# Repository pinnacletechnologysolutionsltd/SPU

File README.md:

# SPU

SPU is an experimental computing architecture exploring how exact algebraic
arithmetic, geometric representations and deterministic transformations can
support useful native computational primitives.

The [research identity](docs/RESEARCH_IDENTITY.md) defines **Demonstrated**,
**Experimental** and **Exploratory** claims and the evidence needed for utility
in correctness, determinism, speed, energy, verification or system complexity.

Architectural invention is the ambition; demonstrated utility is the test.

## SPU v0.2: canonical machine, the Gen-1 Surd CPU

Each SPU release identifies one canonical machine, its architectural contract and
the evidence for it. For v0.2 that machine is the **Gen-1 Surd CPU**. It is
deliberately narrow, and it is the reference point for everything this release
claims about the processor.

| Property | SPU v0.2 |
|---|---|
| Machine | Frozen Gen-1 Surd CPU ([architectural contract](docs/GEN1_ARCHITECTURAL_CONTRACT.md); [source package](hardware/boards/artix7/wukong_v3/cpu_v02/README.md)) |
| Arithmetic | Exact multiplication in Q(√3), (a + b√3)/d with 64-bit fields: raw results that fit are committed unreduced, otherwise exact normalization-to-fit, otherwise refusal |
| Programming model | One architectural register (S0); four accepted instruction forms (SLI, SLD, SMUL, SRD); a fixed 14-instruction ROM program built into the bitstream; no control flow |
| Output | One 33-byte UART frame per reset (success or fault) |
| FPGA | Artix-7 XC7A100T on a Wukong V3 board, configured over JTAG into SRAM |
| Simulator | C++ `spu_vm --profile gen1-surd` ([usage](docs/software_guide.md)); conforms to the registered RTL fixtures and recorded silicon frames (software conformance only) |
| Physical status | Experimental single-unit observations: golden program and operand variants, repeated reloads, scoped reset recovery (ledger §3.40–3.43, §3.47–3.49, §3.51–3.52, starting at [§3.40](docs/hardware_evidence.md#340--cpu-board-4c-r1-first-fixed-program-surd-cpu-run-over-uart-2026-10-30)); nominal routed timing analysis; bit-exact rebuild of the configuration payload |
| Not established | General CPU qualification, flash boot, I/O and reset timing, metastability, multiple units |
| Release status | SPU v0.2.0, experimental Gen-1 Surd CPU; see the [v0.2.0 release](https://github.com/pinnacletechnologysolutionsltd/SPU/releases/tag/v0.2.0) and the [readiness record](docs/V02_RELEASE_READINESS.md#12-publication-record-2026-11-11) |

## SPU v0.3: programmable-surd CPU (in preparation)

This branch adds the v0.3 `programmable-surd` machine beside the v0.2 Gen-1 CPU above. v0.3 is a
programmable exact-arithmetic processor with a verified toolchain. It is experimental, it makes no
performance claim, and this branch has not been published as a release.

| Property | SPU v0.3 (`programmable-surd`) |
|---|---|
| Contract | [Frozen v0.3 contract](docs/design/SPU_V03_CONTRACT_CANDIDATE.md): the authoritative ISA. The other `SPU_V03_*` design records in `docs/design/` are historical provenance, not current requirements |
| Machine | Sequential, multicycle, in-order; eight Surd registers S0–S7; programs of 1–256 words; no data memory |
| Arithmetic | Bounded exact Q(√3), (a + b√3)/d with 64-bit fields. A refused `SMUL`, `SADD` or `SSUB` leaves its destination unchanged and sets the refusal flags; the program must check them |
| Inputs | A program image and an instruction budget, supplied by the host. There is no general runtime operand input: input values are part of the image |
| Tools | [SDK](software/sdk/README.md) (assembler, disassembler, `spu` CLI), C++ `spu_vm --profile programmable-surd`, a Python oracle and a UART host client |
| Examples | [`software/sdk/examples/`](software/sdk/examples/): exact √3 arithmetic (Pell K=33), exact orientation, and a refusal-and-recovery branch (Pell K=34) |
| Physical status | One recorded session on one Wukong unit and one SDK-driven run (ledger §3.53 and §3.54 in [`docs/hardware_evidence.md`](docs/hardware_evidence.md)): observations, not a qualification |
| Not established | Qualification of the UART interface, timing margin or reset behaviour; operation across reloads, supply or temperature; multiple units |

The rational GPU, HEX-SOM, the experimental H0 programmable image and the wider
mathematical research below are **experimental components**. They are not
features of the canonical CPU.

Where any historical document in this repository (for example earlier ISA, rotor or accelerator descriptions) conflicts with the Gen-1 architectural contract, the contract is authoritative for v0.2; historical documents are kept for provenance, not as descriptions of supported hardware.

## What is here

- **A software stack.** A Python virtual machine, a C++ VM with the `gen1-surd`
  profile for the canonical machine, an assembler, an exact robotics chain and an
  offline GPU model, all runnable without any hardware.
- **Verilog and FPGA builds** for Tang Primer 25K and Wukong Artix-7 boards. The
  canonical v0.2 machine is the Gen-1 Surd CPU above. The experimental H0
  programmable image is a separate configuration with its own single-session
  observation, not part of the canonical release.
- **Exact-geometry and classification work**, with its limits stated in the
  [capability matrix](docs/CAPABILITY_MATRIX.md), which separates mathematical
  argument, host software, RTL simulation, FPGA synthesis and physical hardware,
  because none implies another.

## Try it in two minutes

You need Python 3.10 or newer and Git. Cloning requires network access; the
commands that follow run locally without a board or package installation.
This README describes the curated `release/v0.3` branch, which carries the v0.2 release
content plus the v0.3 additions listed above; other branches may contain a different snapshot.

```bash
git clone https://github.com/pinnacletechnologysolutionsltd/SPU.git && cd SPU
python3 software/spu_vm_test.py          # ends with "N passed, 0 failed" and PASS
python3 -m software.spu_gpu_eval.cli device-preview examples/gpu/t1d_two_triangle.json \
    --out build/gpu_evaluation/first_run
python3 -m software.spu_gpu_eval.cli inspect examples/gpu/t1d_two_triangle.json --x 320 --y 0
```

The second command renders a two-triangle scene twice: once as an exact mathematical
reference and once through a finite-width model of the GPU's depth arithmetic. Open
`build/gpu_evaluation/first_run/device_preview.ppm` in any image viewer. The last command
shows one pixel where both paths agree on the winner and colour but differ in depth
(2000 versus 1999). The [software quickstart](docs/NEWCOMER_SOFTWARE_QUICKSTART.md) lists more
commands, including a robotics chain and a scene edit, with expected output. Use a new
`--out` directory for each run.

## Known limitations

State these before citing any result:

- **The CPU is not qualified.** The Gen-1 evidence consists of single-unit board
  observations of a fixed program, plus nominal timing analysis. It does not cover
  general correctness, flash boot, I/O or reset timing, or more than one board. The
  separate experimental H0 image ran two UART-loaded programs in one session
  ([§3.46](docs/hardware_evidence.md#346--h0-board-uart-3b-first-uart-loaded-programmable-h0-cpu-run-on-wukong-2026-11-03-utc)).
  That is not a qualification of the CPU, UART or timing margins.
- **The SOM RTL has a full-domain arithmetic defect.** For some inputs the uploader accepts, the
  current classifier RTL can return wrong distances without a flag. The Iris board evidence lies
  inside the safe region. An exact portable C reference that detects the unsafe cases has been written but is
  not part of this release; the RTL itself is not repaired.
- **A negative memory-layout result.** In a model-only cache study, hierarchical hexagonal layouts
  did not beat dense axial addressing overall, and the proposed adaptive weighting did not beat LRU/LFU.
- **Relational and hexagonal geometry are experimental, not a demonstrated speedup.** Fewer exact
  tests were counted in bounded fixtures; no runtime, energy or hardware advantage over a strong
  conventional baseline is shown.
- **Software is not hardware.** The VM and the GPU model run on a host CPU. Physical claims exist only
  in the [hardware evidence ledger](docs/hardware_evidence.md).

Details and evidence boundaries: [capability matrix](docs/CAPABILITY_MATRIX.md#known-limitations).
The [H0 overview](docs/H0_OVERVIEW.md) separates the earlier simulation from
the later board observation.

## Gen-1 CPU progress

The preserved Wukong CPU sources include a board-local core copy with a
driver-conflict fix. That fix has not been promoted to the shared core; see the
[source package](hardware/boards/artix7/wukong_v3/cpu_v02/README.md). The
fixed-program CPU and ROM variants produced expected UART records in separate,
limited board runs ([ledger §3.40–3.43, §3.49](docs/hardware_evidence.md#340--cpu-board-4c-r1-first-fixed-program-surd-cpu-run-over-uart-2026-10-30)).
Later entries record repeated reloads, KEY0 restarts and scoped timed-pulse reset
recovery of the golden image (§3.47, §3.48, [§3.52](docs/hardware_evidence.md#352--gen1-reset-edge-1-timed-key0-reset-recovery-of-the-golden-gen-1-image-2026-11-08-utc)). Nominal routed
static timing analysis passed ([GEN1-STA-1](docs/GEN1_STA_1_CLOSURE_2026-11-07.md)).
The later experimental H0 image accepted two 14-word programs over UART and
returned oracle-matching results in one session ([§3.46](docs/hardware_evidence.md#346--h0-board-uart-3b-first-uart-loaded-programmable-h0-cpu-run-on-wukong-2026-11-03-utc)).

A separate Vivado rebuild reproduced the fixed-program image's configuration
payload bit-for-bit in one attempt; it was not a new board run ([reproduction
record](hardware/boards/artix7/wukong_v3/cpu_v02/portable/REPRO_1B_RESULT.md)).
A second single run on a different host produced the same payload, with no
report differences against the golden build ([desktop
record](docs/CPU_REPRO_DESKTOP_2026-11-06.md)).
That later result supersedes the source package README's earlier statement that
the package had not been rebuilt.
These results demonstrate the recorded programs and images, not general CPU
correctness, interface qualification or measured timing margins.

## Recent development

- The experimental H0 work includes a host transaction model, RTL controller and
  UART loading path. The board observation above covers only the stated image and
  session; simulation, tool timing and physical evidence remain separate.
- Symbolic representation, geometry and nonlinear relational bounds are being
  investigated under [research](research/). These are bounded experiments, not
  architectural guarantees or demonstrated performance gains.
- The [simulator integration policy](docs/SIMULATOR_INTEGRATION_POLICY.md)
  sets conformance and capability-manifest requirements for future releases;
  the policy itself does not establish that current builds satisfy them.

## Reproduce, review, contribute

Independent checks are the most useful contribution right now: run the quickstart, try to break an
oracle or a bound, or add a ledger entry for hardware you own. See
[CONTRIBUTING.md](CONTRIBUTING.md#ways-to-help). Questions and results are welcome on the
[issue tracker](https://github.com/pinnacletechnologysolutionsltd/SPU/issues).

## How this project is developed

The SPU repository is directed and maintained by its owner. Much of the code, tests and documentation were drafted with AI coding assistants
(for example Claude and DeepSeek models) working from specifications and tasks written by the maintainer. Assistant output is run against the
repository's tests and oracles and reviewed by the maintainer before it is committed, and the maintainer is responsible for what is published.
The depth of review has varied across the project's history; the test suite, the evidence ledger and the capability matrix, not the use of any
particular tool, are the basis for what this repository claims.

Commits made with an assistant may carry a `Co-Authored-By` trailer. That trailer records the tooling used. It is not a statement about who owns
copyright and it is not a certification of origin; this project does not retroactively add `Signed-off-by` lines to earlier commits.

### Historical Git Identity and AI-Assisted Development

In the original development repository, some historical commits use the Git identity `john@spu13.local`; this release has a fresh, squashed history that does not include them.

This was a local Git identity used during AI-assisted development sessions. It does not represent an independently verified human contributor, nor should it be interpreted as evidence of independent review or approval.

As project maintainer, I accept responsibility for the changes I select and publish, including AI-assisted contributions. AI assistance does not transfer responsibility for the project's published code, documentation, research claims, or licensing obligations.

Historical commits have been preserved without rewriting Git history, maintaining the continuity of commit identities, validated release artifacts, and existing references.

This disclosure does not imply that another person authored or signed off on these changes.

## Where to go next

- [Short introduction](docs/START_HERE.md): the ideas, a worked example, current results and their limits.
- [Documentation index](docs/index.md) and the [capability matrix](docs/CAPABILITY_MATRIX.md).

Licensing varies by component; see [LICENSING.md](LICENSING.md).

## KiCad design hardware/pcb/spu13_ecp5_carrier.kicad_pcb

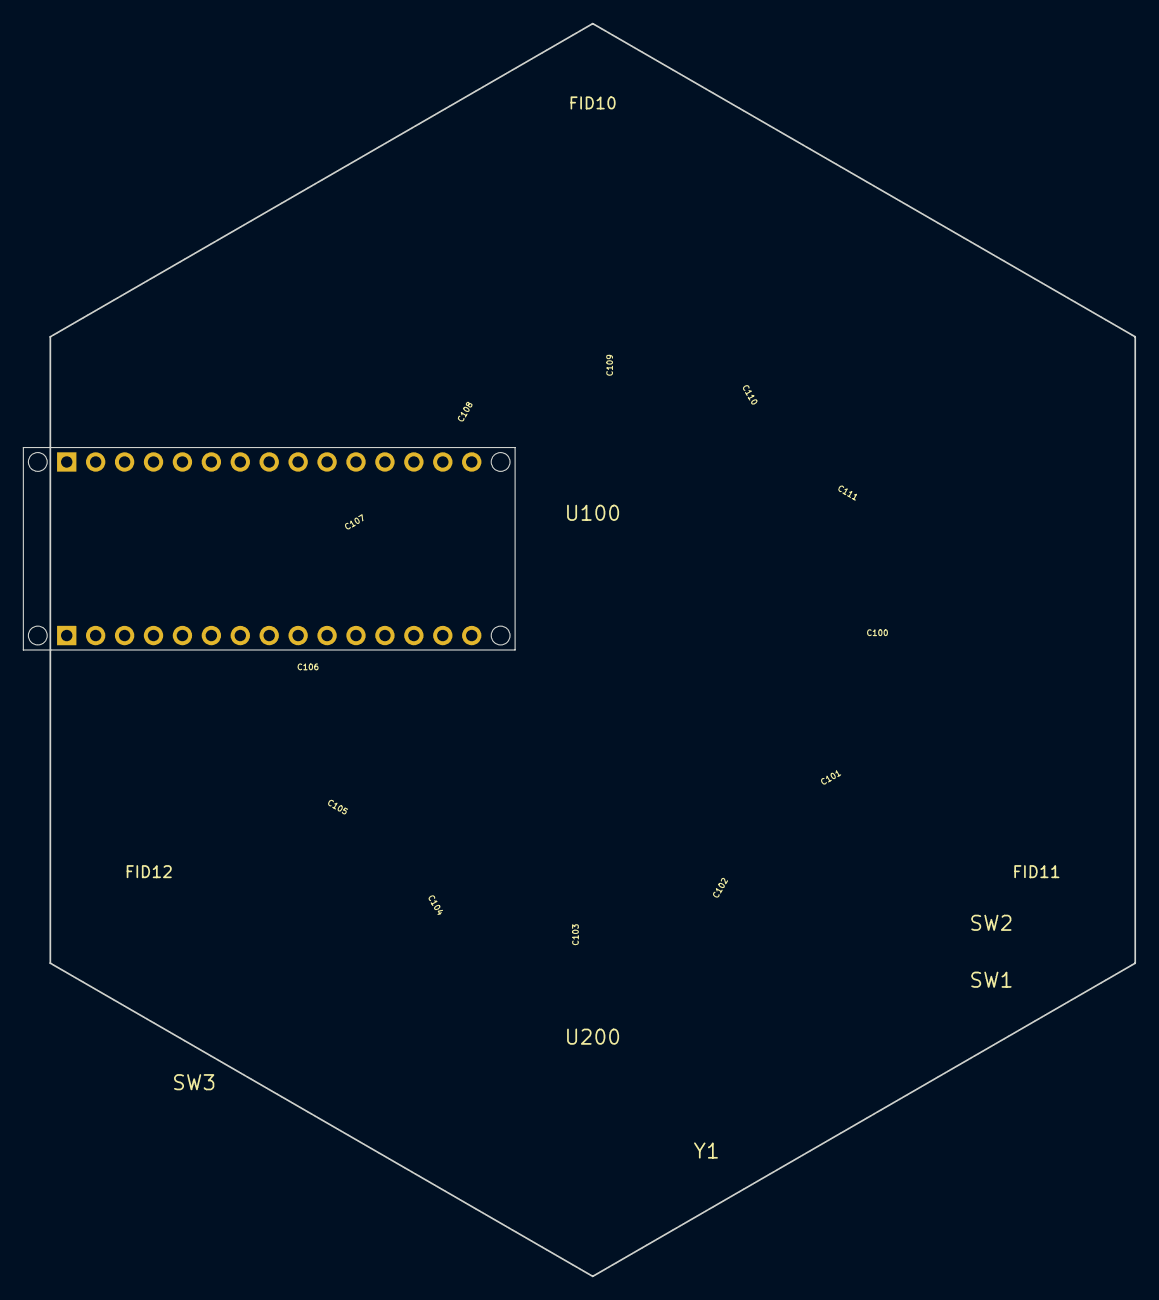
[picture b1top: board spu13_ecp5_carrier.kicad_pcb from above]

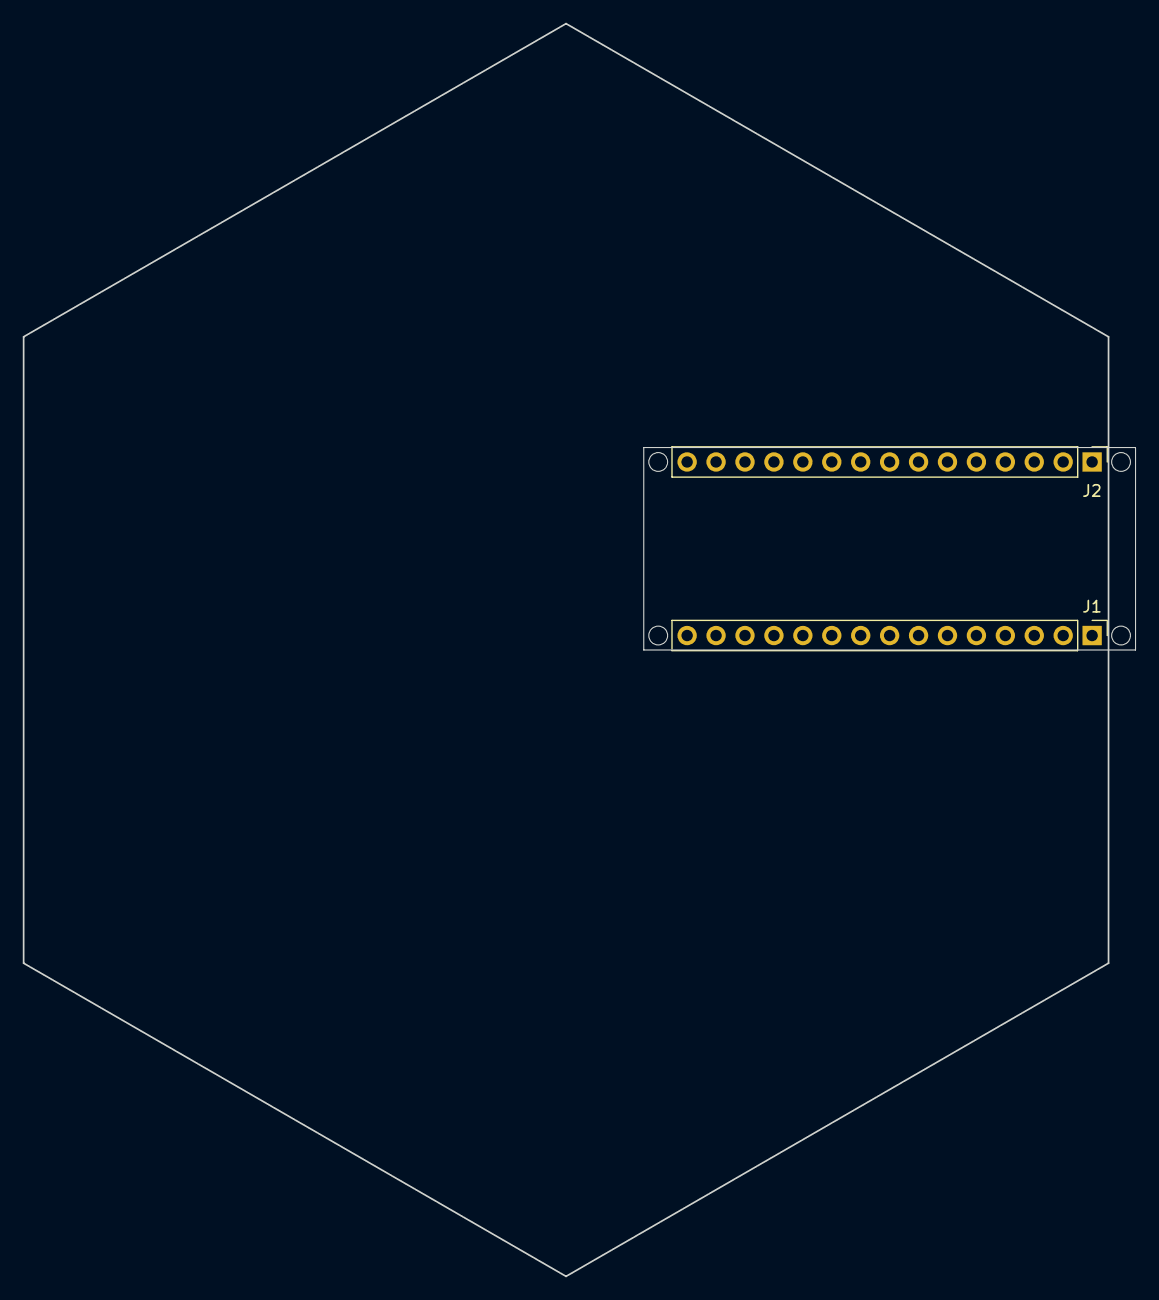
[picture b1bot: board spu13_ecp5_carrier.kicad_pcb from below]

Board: 2 copper layers, 97.6 x 110.0 mm, 27 parts (2 on the bottom side), 2 nets, no tracks yet.

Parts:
C100, C101, C102, C103, C104, C105, C106, C107, C108, C109, C110, C111: 100nF; C_0402_1005Metric
FID10, FID11, FID12: FID; Fiducial_1.5mm_Dia_2.5mm_Outer
J1: Analog; PinHeader_1x15_P2.54mm_Vertical
J2: Digital; PinHeader_1x15_P2.54mm_Vertical
MH1, MH2, MH3, MH4: MountingHole_65mil
SW1: BOOT; SW_Push_1P1T_NO_6x6mm_H5.0mm
SW2: RUN; SW_Push_1P1T_NO_6x6mm_H5.0mm
SW3: MODE; SW_DIP_SPSTx04_Slide_CTS_219-4MST_1.27x7.3mm
U100: LFE5UM-85F; LFBGA-381_17.0x17.0mm_Layout20x20_P0.8mm
U200: RP2350; QFN-60-1EP_7x7mm_P0.4mm_EP5.15x5.15mm
Y1: 12MHz; Crystal_SMD_3225-4pin_3.2x2.5mm

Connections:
/~RESET: J1.13, J2.13
GND: J1.14, J2.12
